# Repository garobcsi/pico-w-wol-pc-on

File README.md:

# Turn on your pc useing a raspberry pico-w

## Main goal of the project

Some motherboards dosent support wol or just dosent always work,
but useing a pico as the wol reciver (the pico connects to wifi) you could turn on your pc from anywhere in the world if you use port forwarding on your router.

## Thecnical side

### main.c

In `#define` setup your `SSID` `PASSWORD` and your `GPIO_PIN` number has to be configured and then build the firmweare.

#### Building the firmweare

```
cd code
cmake .
make
```

### The pico and motherboard

When the pico recives a magic packet it send a signal to the optocoupler (the pico cannot be on the same ground as your pc) and briges the power button and turns on the pc. But thers a pass truh port that you plug in your existing pc's power button so the pc's power button dosent lose it's function. And the pc can be turn on by existing button and by the pcio.

`Wol in`: pico gpio input
`BT in`: pc case power button
`FP out`: front panel out

## Motherboard pics

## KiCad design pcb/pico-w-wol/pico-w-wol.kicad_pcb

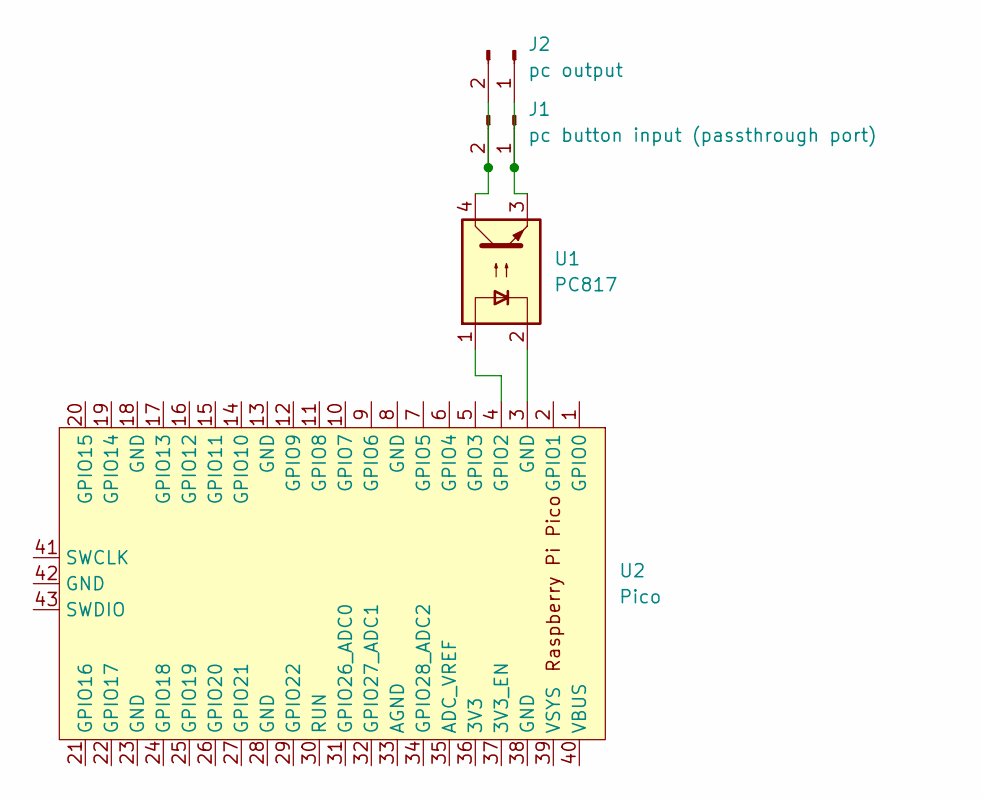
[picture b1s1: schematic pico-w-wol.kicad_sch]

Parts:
J1: pc button input (passthrough port); PinHeader_1x02_P2.54mm_Vertical
J2: pc output; PinHeader_1x02_P2.54mm_Vertical
U1: PC817; DIP-4_W7.62mm
U2: Pico; RPi_Pico_SMD_TH

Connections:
unnamed: J1.1, J2.1, U1.3
unnamed: J1.2, J2.2, U1.4
unnamed: U1.2, U2.3 (GND)
unnamed: U1.1, U2.4 (GPIO2)

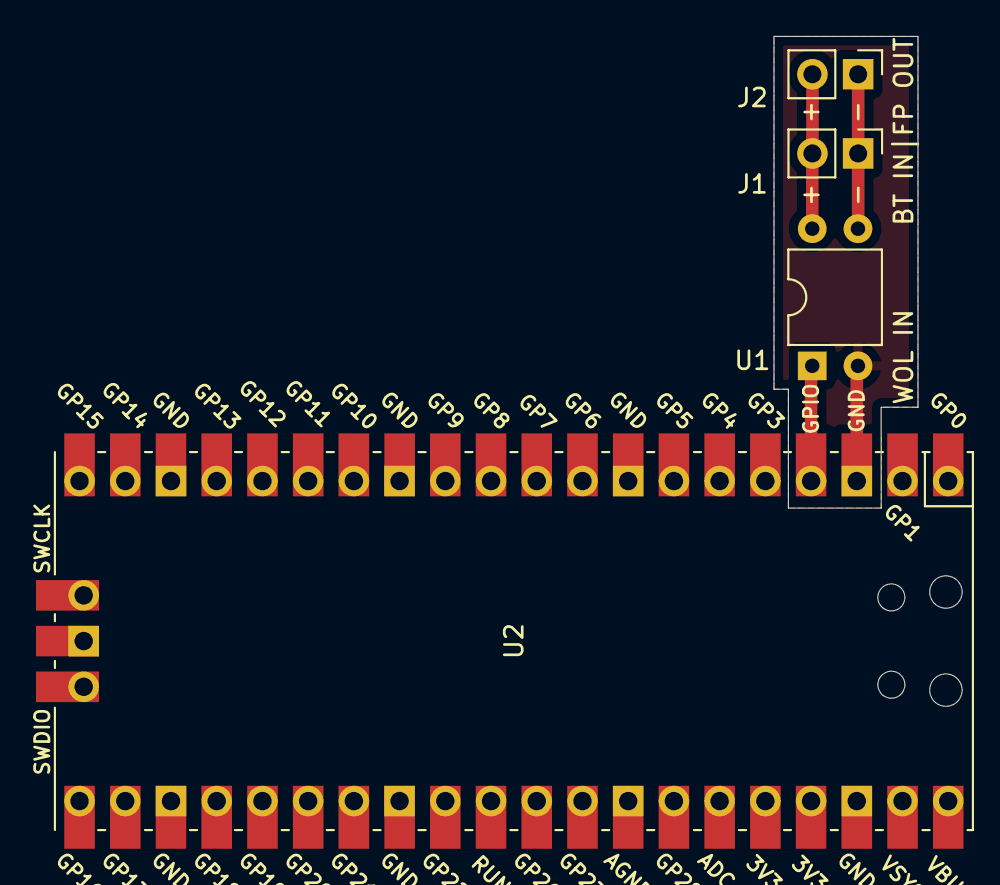
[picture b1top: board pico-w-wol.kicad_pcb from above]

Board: 2 copper layers, 4 parts (0 on the bottom side), 4 nets.

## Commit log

2024-07-29 Made hello world and setup compiler
2024-07-29 added cmake to build uf2 and extended hello world
2024-07-29 Fixed building
2024-07-29 Updated cmake
2024-07-29 Fixed build nameing
2024-07-29 made wol to led
2024-07-30 moved code and created pcb
2024-07-30 added blink gpio pin
2024-07-30 fixed gpio output
2024-07-30 Updated pcb labeling
2024-07-30 Create LICENSE
2024-07-30 Updated silkscreen
2024-07-30 Added readme
2024-08-01 added defines
2024-08-01 added wifi conection error handling
2024-08-13 fixed gpio bug
